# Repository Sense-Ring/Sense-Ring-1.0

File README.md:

# SenseRing

**Open-source smart ring for biosensing and motion tracking, packed into a format you can build, program, and improve.**

SenseRing is a compact, finger-worn research and development platform built around the Nordic Semiconductor [nRF52832](https://www.nordicsemi.com/Products/nRF52832) Bluetooth Low Energy SoC. Its custom electronics combine optical pulse sensing, motion sensing, wireless connectivity, battery charging, and power management in a wearable form factor.

Use it to explore photoplethysmography (PPG), heart-rate and SpO₂ algorithm development, activity and gesture recognition, low-power Bluetooth applications, and new wearable interfaces. 

> [!IMPORTANT]
> SenseRing is an experimental research platform, not a certified medical device. Do not use it for diagnosis, treatment, or safety-critical monitoring.

## Hardware features

| Function | Implementation |
| --- | --- |
| Processing and wireless | [nRF52832](https://www.nordicsemi.com/Products/nRF52832), 64 MHz Arm Cortex-M4F with Bluetooth Low Energy and a 2.4 GHz radio |
| Optical sensing | [MAX30102](https://www.analog.com/en/products/max30102.html) integrated red/IR PPG sensor for pulse-oximetry and heart-rate experiments |
| Motion sensing | [BMA530](https://www.bosch-sensortec.com/en/products/motion-sensors/accelerometers/bma530) ultra-compact, low-power 3-axis accelerometer with motion interrupts and step-counting support |
| Battery charging | [BQ25180](https://www.ti.com/product/BQ25180) single-cell Li-ion/LiPo charger with I²C control, power path, and ship mode |
| Power and protection | [AP6683](https://www.lcsc.com/datasheet/C2849565.pdf) battery protection, [XC6504A1819R-G](https://www.lcsc.com/datasheet/C5142782.pdf) 1.8 V LDO, and two [WS4622C](https://www.lcsc.com/datasheet/C2939859.pdf) load switches for the PPG LED supply and battery-measurement circuit |
| RF front end | [2450AT18B100E](https://www.lcsc.com/datasheet/C2917717.pdf) 2.4 GHz chip antenna and matching circuit |
| Debugging and test | TC2030 SWD footprint for programming and charging, compatible with [Segger J-Link 6-pin Needle Adapters](https://www.segger.com/products/debug-probes/j-link/accessories/adapters/6-pin-needle-adapter/) |
|Battery| 31mAh curved [GRP1607034](https://www.grepow.com/wearables/smart-ring.html)|
| PCB | 14.9 × 10 mm, two copper layers, mostly fine-pitch WLCSP and 0201 components |

## Architecture

The nRF52832 communicates with the PPG sensor, accelerometer, and charger over a shared I²C bus. Dedicated interrupt lines allow the sensors and PMIC to wake the processor. The PPG LED supply and battery-measurement divider are independently switchable, limiting leakage when those functions are idle.

| Signal | nRF52832 pin | Connected function |
| --- | --- | --- |
| `SDA` | `P0.29 / AIN5` | MAX30102, BMA530, and BQ25180 data |
| `SCL` | `P0.28 / AIN4` | MAX30102, BMA530, and BQ25180 clock |
| `PPG_INT` | `P0.06` | MAX30102 interrupt |
| `IMU_INT` | `P0.18` | BMA530 interrupt |
| `PMIC_INT` | `P0.15` | BQ25180 interrupt |
| `LED_EN` | `P0.01` | PPG LED-rail load switch |
| `VBAT_EN` | `P0.00` | Battery-divider load switch |
| `VBAT_MEAS` | `P0.05 / AIN3` | Battery-voltage ADC input |
| `TX` test pad | `P0.30 / AIN6` | Firmware-assignable test/UART signal |
| `RX` test pad | `P0.25` | Firmware-assignable test/UART signal |

## Battery benchmark

Measured with a Power Profiler Kit II supplying the board in place of the 31 mAh cell, running the normal cycle: 15 s window, five readings, LED rail down, 90 s pause. IMU on throughout, BLE advertising. This replaces the estimate in [`ARCHITECTURE.md`](Software/Firmware/src/ARCHITECTURE.md) §5.1.1 (~305 µA, four days).

| Mode | Average load current | Duration |
| --- | --- | --- |
| Sampling (LED rail up) | 1.35 mA | 31 s |
| Sleep (IMU and BLE only) | 0.07 mA | 90 s |
| **Full cycle** | **0.41 mA** | **121 s** |

31 s of sampling against a 90 s pause is 25.6 % duty. Over ten minutes the capture reads 410.55 µA average, 246.33 mC, 14.85 mA peak. One full pause reads 62.75 µA: the BMA530 at ~15 µA, the nRF52832 idle, and both load switches open.

### Runtime on 31 mAh

| Quantity | Value |
| --- | --- |
| Charge per cycle | 13.7 µAh (~49 mC) |
| Cycles per charge | ~2,250 |
| Readings per charge | ~11,250 |
| **Runtime, default cadence** | **~75 h (3.1 days)** |
| Sampling continuously | ~23 h |
| Sleep floor only | ~440 h (18 days) |

## Repository contents

| Path | Contents |
| --- | --- |
| [`Hardware/`](Hardware/) | Autodesk Fusion Electronics/EAGLE schematic and board sources (`.fsch`, `.fbrd`, `.sch`, `.brd`) and a [schematic PDF](Hardware/SenseRing_schematic.pdf) |
| [`Mechanical/`](Mechanical/) | Complete Fusion 360 archive, STEP and OBJ assemblies, printable shell STLs, board and battery models, and two programming-fixture STLs |
| [`Images/`](Images/) | Prototype photographs and the exploded assembly render used in this README |
| [`Software/Firmware/`](Software/Firmware/) | nRF52832 firmware: sampling, the vitals estimator, the flash log, and the BLE peripheral |
| [`Software/App/`](Software/App/) | Android companion app: collects the ring's buffered log over BLE, stores it locally and charts it |

## Working with the design

### 1. Clone the repository

```bash
git clone https://github.com/Sense-Ring/Sense-Ring-1.0.git
cd Sense-Ring-1.0
```

### 2. Inspect or modify the electronics

- Open [`SenseRing.fsch`](Hardware/SenseRing.fsch) and [`SenseRing.fbrd`](Hardware/SenseRing.fbrd) in Autodesk Fusion Electronics.
- The XML [`SenseRing.sch`](Hardware/SenseRing.sch) and [`SenseRing.brd`](Hardware/SenseRing.brd) files are also included for EAGLE-compatible workflows.
- For a quick review without CAD software, open [`SenseRing_schematic.pdf`](Hardware/SenseRing_schematic.pdf).

### 3. Inspect or print the enclosure

- Open [`RingCase.f3z`](Mechanical/RingCase.f3z) for the editable Fusion 360 assembly.
- Use [`RingCase.step`](Mechanical/RingCase.step) or [`RingCase.obj`](Mechanical/RingCase.obj) for interchange with other CAD tools.
- Print [`InnerShell.stl`](Mechanical/InnerShell.stl) and [`OuterShell.stl`](Mechanical/OuterShell.stl) for the enclosure.
- The repository also provides board and battery reference models and two-piece programming-fixture STLs.

### 4. Program and debug

The PCB exposes `SWDIO`, `SWDCLK`, `RESET`, 1.8 V, +5 V, and GND through its TC2030 programming footprint. Use a compatible SWD debugger and verify the target-voltage and power configuration before connecting it to the board.

## Manufacturing notes

This is a miniaturized wearable design using WLCSP/BGA packages and 0201 passives. Professional PCB assembly and appropriate inspection equipment are strongly recommended.

The current repository does **not** include production exports such as Gerbers, drill files, a bill of materials, or pick-and-place data. Generate and verify those outputs from the hardware sources before ordering boards. Battery selection, charge settings, clearances, enclosure material, skin contact, RF performance, and optical performance must all be validated for your implementation.

## Contributing

Issues, design reviews, firmware ports, enclosure variants, measurements, and reproducibility notes are welcome. When reporting a hardware problem, please include the board revision, power source, programmer/debugger, and enough measurements or logs to reproduce it.

## License

SenseRing 1.0 is open source and distributed under the [GNU General Public License v3.0](LICENSE). It is provided as-is, without warranty.

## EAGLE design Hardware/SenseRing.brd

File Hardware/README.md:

Hardware design files for Fusion 360 / Eagle CAD

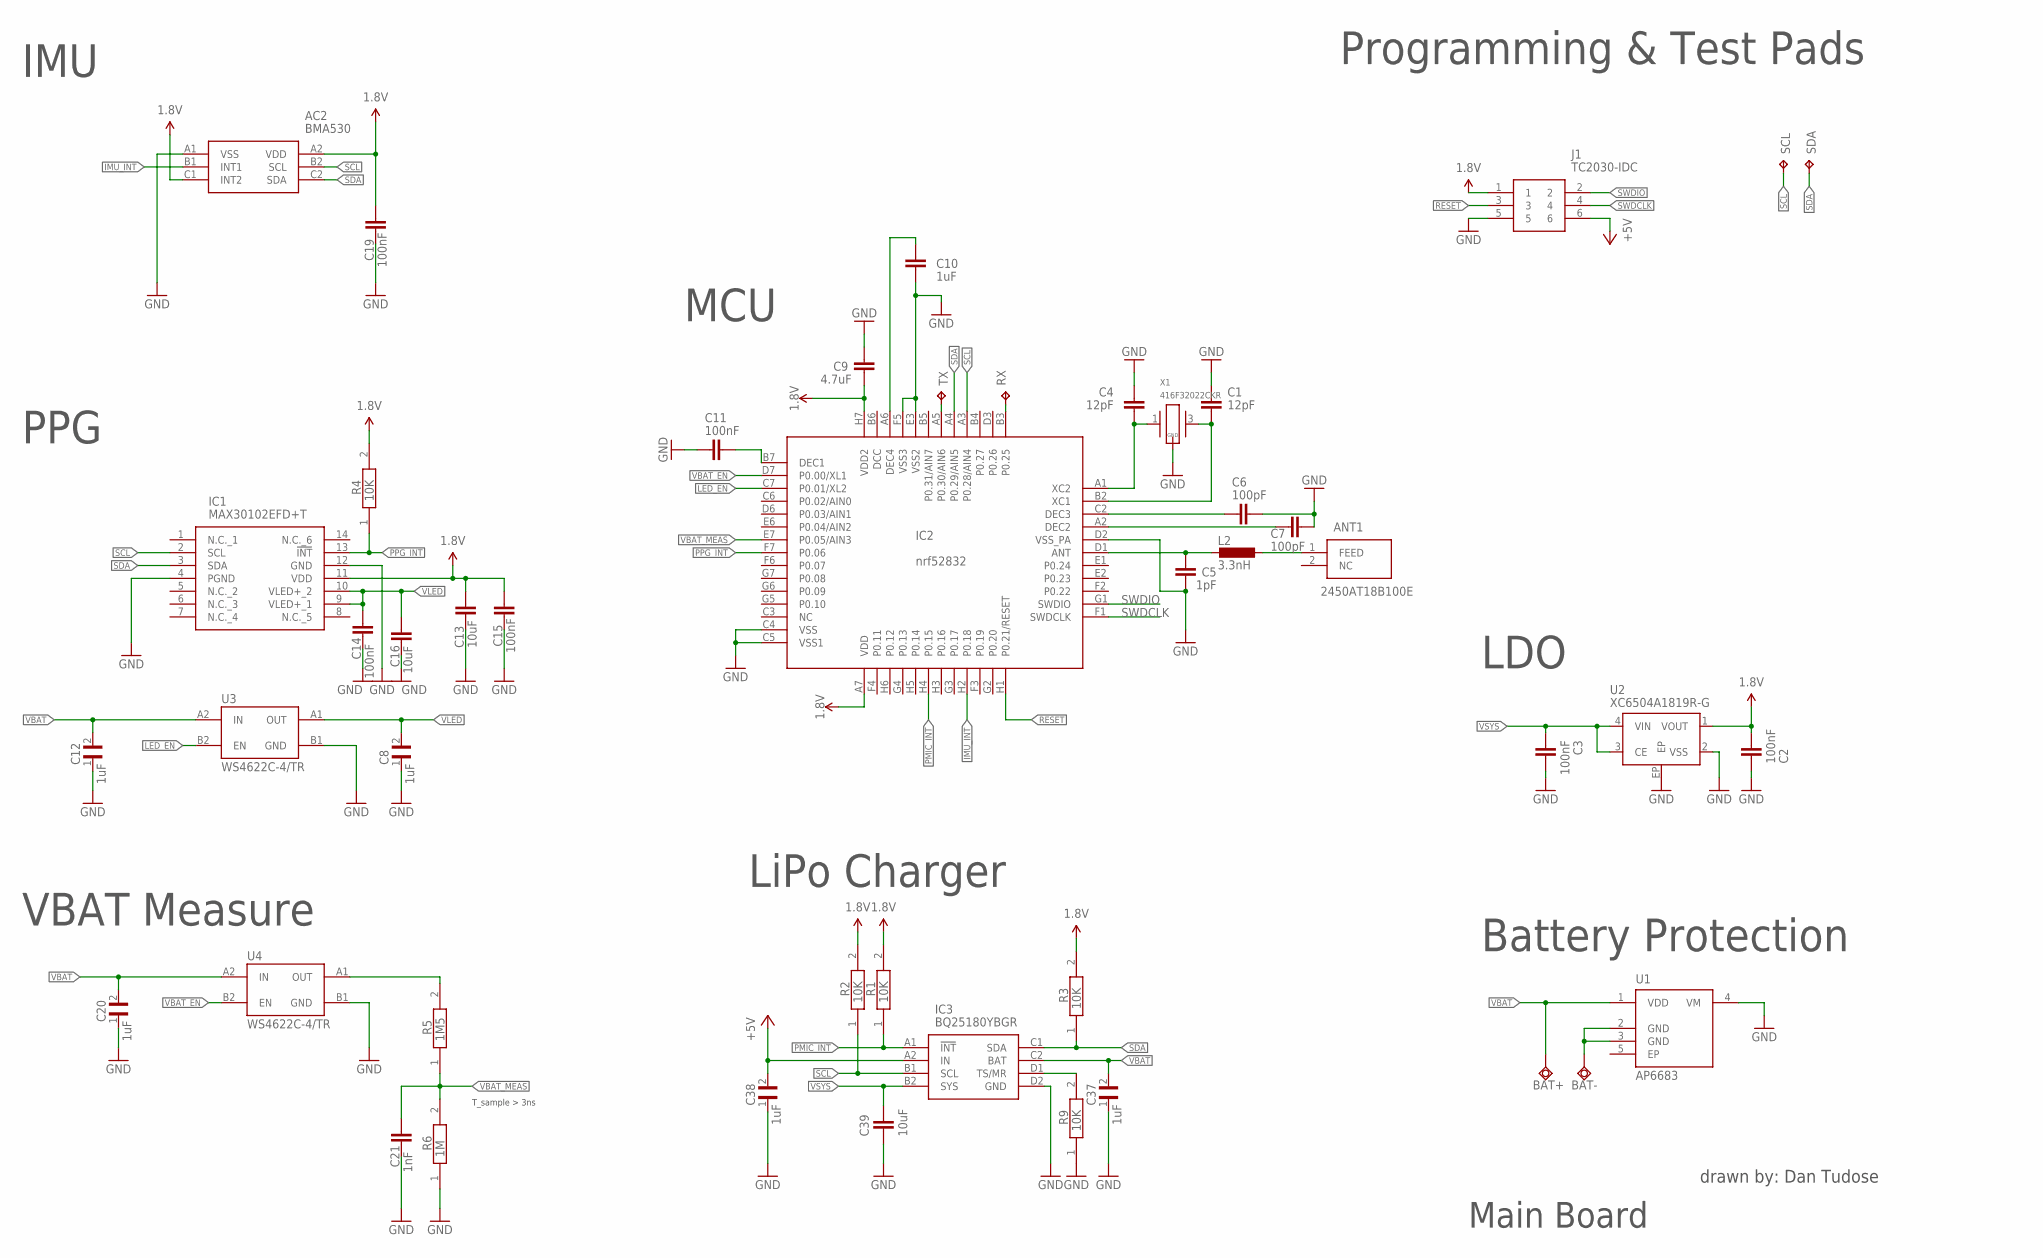
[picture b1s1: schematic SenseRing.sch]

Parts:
AC2: BMA530
ANT1: 2450AT18B100E; ANTC3216X140N
BAT+: TPSQTP10SQ; TP10SQ
BAT-: TPSQTP10SQ; TP10SQ
C1, C4: 12pF; C0201
C2, C3, C11, C14, C15, C19: 100nF; C0201
C5: 1pF; C0201
C6, C7: 100pF; C0201
C8, C12, C20, C37, C38: 1uF; 0201
C9: 4.7uF; C0201
C10: 1uF; C0201
C13, C16, C39: 10uF; 0402
C21: 1nF; C0201
IC1: MAX30102EFD+T; MAX30102EFDT
IC2: nrf52832; NRF52832_WLCSP
IC3: BQ25180YBGR; BGA8C40P2X4_100X155X50
J1: TC2030-IDC; TC2030IDC
L2: 3.3nH; L0201
R1, R2, R3, R4, R9: 10K; 0201
R5: 1M5; 0201
R6: 1M; 0201
RX: TPTP06R; TP06R
SCL: TPTP06R; TP06R
SDA: TPTP06R; TP06R
TX: TPTP06R; TP06R
U1: AP6683; DFN-4_L1.0-W1.0-P0.65-BL-EP
U2: XC6504A1819R-G; USPQ-4B04
U3, U4: WS4622C-4/TR; CSP-4L_1X1
X1: 416F32022CKR; M416

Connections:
1.8V: AC2.A2 (VDD), AC2.C1 (INT2), C2.1, C9.2, C13.1, C15.2, C19.2, IC1.11 (VDD), IC2.A7 (VDD), IC2.H7 (VDD2), J1.1, R1.2, R2.2, R3.2, R4.2, U2.1 (VOUT)
+5V: C38.2, IC3.A2 (IN), J1.6
GND: AC2.A1 (VSS), C1.1, C2.2, C3.1, C4.1, C5.2, C6.2, C7.2, C8.1, C9.1, C10.2, C11.2, C12.1, C13.2, C14.1, C15.1, C16.2, C19.1, C20.1, C21.1, C37.1, C38.1, C39.2, IC1.4 (PGND), IC1.12 (GND), IC2.C4 (VSS), IC2.C5 (VSS1), IC2.D2 (VSS_PA), IC2.E3 (VSS2), IC2.F5 (VSS3), IC3.D2 (GND), J1.5, R6.1, R9.1, U1.4 (VM), U2.2 (VSS), U2.EP, U3.B1 (GND), U4.B1 (GND), X1.2 (GND), X1.4 (GND)
IMU_INT: AC2.B1 (INT1), IC2.H2 (P0.18)
LED_EN: IC2.C7 (P0.01/XL2), U3.B2 (EN)
unnamed: BAT-.TP, U1.2 (GND), U1.3 (GND)
unnamed: IC2.A5 (P0.30/AIN6), TX.TP
unnamed: IC2.B3 (P0.25), RX.TP
unnamed: C4.2, IC2.A1 (XC2), X1.1
unnamed: C7.1, IC2.A2 (DEC2)
unnamed: C1.2, IC2.B2 (XC1), X1.3 (2)
unnamed: C5.1, IC2.D1 (ANT), L2.2
unnamed: C6.1, IC2.C2 (DEC3)
unnamed: IC3.D1 (TS/MR), R9.2
unnamed: ANT1.1 (FEED), L2.1
unnamed: C11.1, IC2.B7 (DEC1)
unnamed: C10.1, IC2.A6 (DEC4)
PMIC_INT: IC2.H4 (P0.15), IC3.A1 (!INT), R1.1
PPG_INT: IC1.13 (!INT), IC2.F7 (P0.06), R4.1
RESET: IC2.H1 (P0.21/RESET), J1.3
SCL: AC2.B2 (SCL), IC1.2 (SCL), IC2.A3 (P0.28/AIN4), IC3.B1 (SCL), R2.1, SCL.TP
SDA: AC2.C2 (SDA), IC1.3 (SDA), IC2.A4 (P0.29/AIN5), IC3.C1 (SDA), R3.1, SDA.TP
SWDCLK: IC2.F1 (SWDCLK), J1.4
SWDIO: IC2.G1 (SWDIO), J1.2
VBAT: BAT+.TP, C12.2, C20.2, C37.2, IC3.C2 (BAT), U1.1 (VDD), U3.A2 (IN), U4.A2 (IN)
VBAT_EN: IC2.D7 (P0.00/XL1), U4.B2 (EN)
VBAT_MEAS: C21.2, IC2.E7 (P0.05/AIN3), R5.1, R6.2
VBAT_OUT: R5.2, U4.A1 (OUT)
VLED: C8.2, C14.2, C16.1, IC1.9 (VLED+_1), IC1.10 (VLED+_2), U3.A1 (OUT)
VSYS: C3.2, C39.1, IC3.B2 (SYS), U2.3 (CE), U2.4 (VIN)

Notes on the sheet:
T_sample > 3ns
Main Board
drawn by: Dan Tudose
IMU
PPG
VBAT Measure
MCU
Programming & Test Pads
LDO
Battery Protection
LiPo Charger

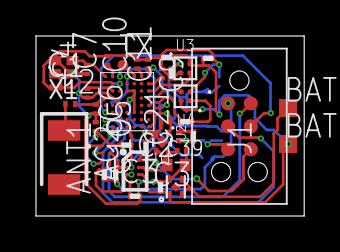
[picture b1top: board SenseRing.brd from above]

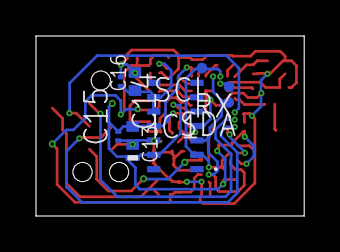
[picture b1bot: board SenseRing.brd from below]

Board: 2 copper layers, 14.9 x 10.0 mm, 47 parts (9 on the bottom side), 30 nets.

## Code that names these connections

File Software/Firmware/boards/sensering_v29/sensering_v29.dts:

/dts-v1/;
#include <nordic/nrf52832_qfaa.dtsi>
#include <zephyr/dt-bindings/adc/adc.h>

/ {
    model = "SenseRing v29";
    compatible = "sensering,sensering-v29";

    chosen {
        zephyr,sram = &sram0;
        zephyr,flash = &flash0;
        /* Keep the settings/NVS backend off the vitals-log partition. Without
         * this it defaults to storage_partition, which flash_store.c erases at
         * boot and laps over in normal running -- taking the BLE bond keys
         * with it.
         */
        zephyr,settings-partition = &settings_partition;
    };

    /* Updated hardware-aware mapping for your load switches */
    power_switches {
        compatible = "gpio-leds";
        led_en_switch: switch_1 {
            gpios = <&gpio0 1 GPIO_ACTIVE_HIGH>; /* Moved from P0.10 -> P0.01 */
            label = "VLED Rail Load Switch Enable";
        };
        vbat_en_switch: switch_2 {
            gpios = <&gpio0 0 GPIO_ACTIVE_HIGH>; /* Moved from P0.09 -> P0.00 */
            label = "Battery Voltage Divider Enable";
        };
    };

    /* Explicitly mapping the hardware interrupt inputs to give names to pins */
    interrupt_signals {
        compatible = "gpio-keys";
        ppg_int_pin: int_ppg {
            gpios = <&gpio0 6 (GPIO_ACTIVE_LOW | GPIO_PULL_UP)>;
            label = "MAX30102 Interrupt Line";
        };
        pmic_int_pin: int_pmic {
            gpios = <&gpio0 15 (GPIO_ACTIVE_LOW | GPIO_PULL_UP)>;
            label = "BQ25180 PMIC Interrupt Line";
        };
        imu_int_pin: int_imu {
            gpios = <&gpio0 18 (GPIO_ACTIVE_LOW | GPIO_PULL_UP)>;
            label = "BMA530 IMU Interrupt Line";
        };
    };

    /* The cell reaches this divider only while vbat_en_switch holds U4 on, so
     * the legs below burn 1.7uA during a reading and nothing at all between
     * them. The tap sits on AIN3.
     */
    vbat: vbat {
        compatible = "voltage-divider";
        io-channels = <&adc 3>;
        output-ohms = <1000000>;  /* R6 */
        full-ohms = <2500000>;    /* R5 (1M5) + R6 (1M) */
    };
};

&flash0 {
    partitions {
        compatible = "fixed-partitions";
        #address-cells = <1>;
        #size-cells = <1>;

        boot_partition: partition@0 {
            label = "mcuboot";
            reg = <0x00000000 0xc000>;
        };
        slot0_partition: partition@c000 {
            label = "image-0";
            reg = <0x0000c000 0x32000>;
        };
        /* What used to be image-1 (200KB) and image-scratch (32KB) is now the
         * vitals log. MCUboot is not built and nothing links against these
         * slots (ARCHITECTURE.md App. C), so before this they were 232KB of
         * flash the device carried and never touched.
         *
         * **The trade, made deliberately: this gives up OTA updates** unless the
         * space is reclaimed later. What it buys is buffer depth -- the ring
         * goes from ~8.6 hours uncollected to a bit over four days, which is
         * the difference between a wearer who leaves their phone charging
         * overnight losing the early hours of a night and losing nothing.
         * That failure is specific and plausible; a firmware update path that
         * has never been built is not.
         *
         * Reclaiming it later means shrinking this back to 0x6000 at 0x7a000
         * and restoring the two slots. Records are RAM-addressed by sequence
         * number and erased at boot, so nothing on flash has to migrate.
         */
        storage_partition: partition@3e000 {
            label = "storage";
            reg = <0x0003e000 0x3a000>;
        };
        /* NVS-backed settings store for BLE bond keys (see CONFIG_BT_SETTINGS).
         * Two pages is the NVS minimum: the backend needs at least two 4KB
         * erase sectors for its garbage collection.
         *
         * **Deliberately left where it was.** The obvious tidier layout moves
         * this to the end and lets storage run contiguously to 0x80000, but the
         * NVS content is addressed by partition offset: moving it discards every
         * stored bond *and* the BLE identity address, so every paired phone
         * would need re-pairing and every standing auto-connect request would be
         * waiting for a peer that no longer exists (§5B.5). Twenty-four
         * kilobytes of buffer is not worth that.
         */
        settings_partition: partition@78000 {
            label = "settings";
            reg = <0x00078000 0x2000>;
        };
        /* 0x7a000-0x80000 is the old 24KB storage partition, now unallocated.
         * It is stranded on the far side of `settings` and cannot be merged
         * into the log, which has to be one contiguous flash area. Left out of
         * the table rather than relabelled, so it reads as spare rather than as
         * something with a purpose.
         */
    };
};

&gpio0 {
    status = "okay";
};

&gpiote {
    status = "okay";
};

&adc {
    status = "okay";
    #address-cells = <1>;
    #size-cells = <0>;

    /* The divider scales a full 4.2V cell down to 1.68V, so 1/3 gain against
     * the internal 0.6V reference gives a 1.8V full scale that covers the cell
     * with a little room left over. R5 and R6 in parallel present 600k to the
     * SAADC, which is why the sampling capacitor needs the longest acquisition
     * window the peripheral offers.
     */
    channel@3 {
        reg = <3>;
        zephyr,gain = "ADC_GAIN_1_3";
        zephyr,reference = "ADC_REF_INTERNAL";
        zephyr,acquisition-time = <ADC_ACQ_TIME(ADC_ACQ_TIME_MICROSECONDS, 40)>;
        zephyr,input-positive = <NRF_SAADC_AIN3>;
        zephyr,resolution = <12>;
        /* The PPG pulses ~10mA of LED drive off the same cell, so average 16
         * conversions to keep that ripple out of the reading.
         */
        zephyr,oversampling = <4>;
    };
};

/* Shared I2C (TWI) Bus Mapping using your updated hardware boundaries */
&i2c0 {
    status = "okay";
    pinctrl-0 = <&i2c0_default>;
    pinctrl-1 = <&i2c0_sleep>;
    pinctrl-names = "default", "sleep";
    clock-frequency = <I2C_BITRATE_FAST>; /* 400 kHz bus clock speed */

    max30102: max30102@57 {
        compatible = "i2c-device";
        reg = <0x57>;
        label = "MAX30102_PPG";
    };

    /* The v49 schematic (designator AC2) fits a BMA530, not the BMA456 this
     * node used to claim. Different part, different generation, incompatible
     * register map. 0x18 is the BMA530's fixed default address -- the 6-ball
     * WLCSP exposes no SDO pin, so unlike the BMA456 there is nothing to strap.
     */
    bma530: bma530@18 {
        compatible = "i2c-device";
        reg = <0x18>;
        label = "BMA530_IMU";
    };
};

/* Pin control management updated from (P0.26/P0.27) -> (P0.29/P0.28) */
&pinctrl {
    i2c0_default: i2c0_default {
        group1 {
            psels = <NRF_PSEL(TWIM_SDA, 0, 29)>,
                    <NRF_PSEL(TWIM_SCL, 0, 28)>;
            bias-pull-up;
        };
    };

    i2c0_sleep: i2c0_sleep {
        group1 {
            psels = <NRF_PSEL(TWIM_SDA, 0, 29)>,
                    <NRF_PSEL(TWIM_SCL, 0, 28)>;
            low-power-enable;
        };
    };
};

&clock {
    status = "okay";
};

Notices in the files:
parts and their libraries:
SparkFun-PowerSymbols: Licensing: Creative Commons ShareAlike 4.0 International - https://creativecommons.org/licenses/by-sa/4.0
